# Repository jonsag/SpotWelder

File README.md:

# SpotWelder

A timed circuit controlling an SSR connected to an old microwave transformer.  

Weld time is displayed on an OLED screen, and set with a rotary encoder.

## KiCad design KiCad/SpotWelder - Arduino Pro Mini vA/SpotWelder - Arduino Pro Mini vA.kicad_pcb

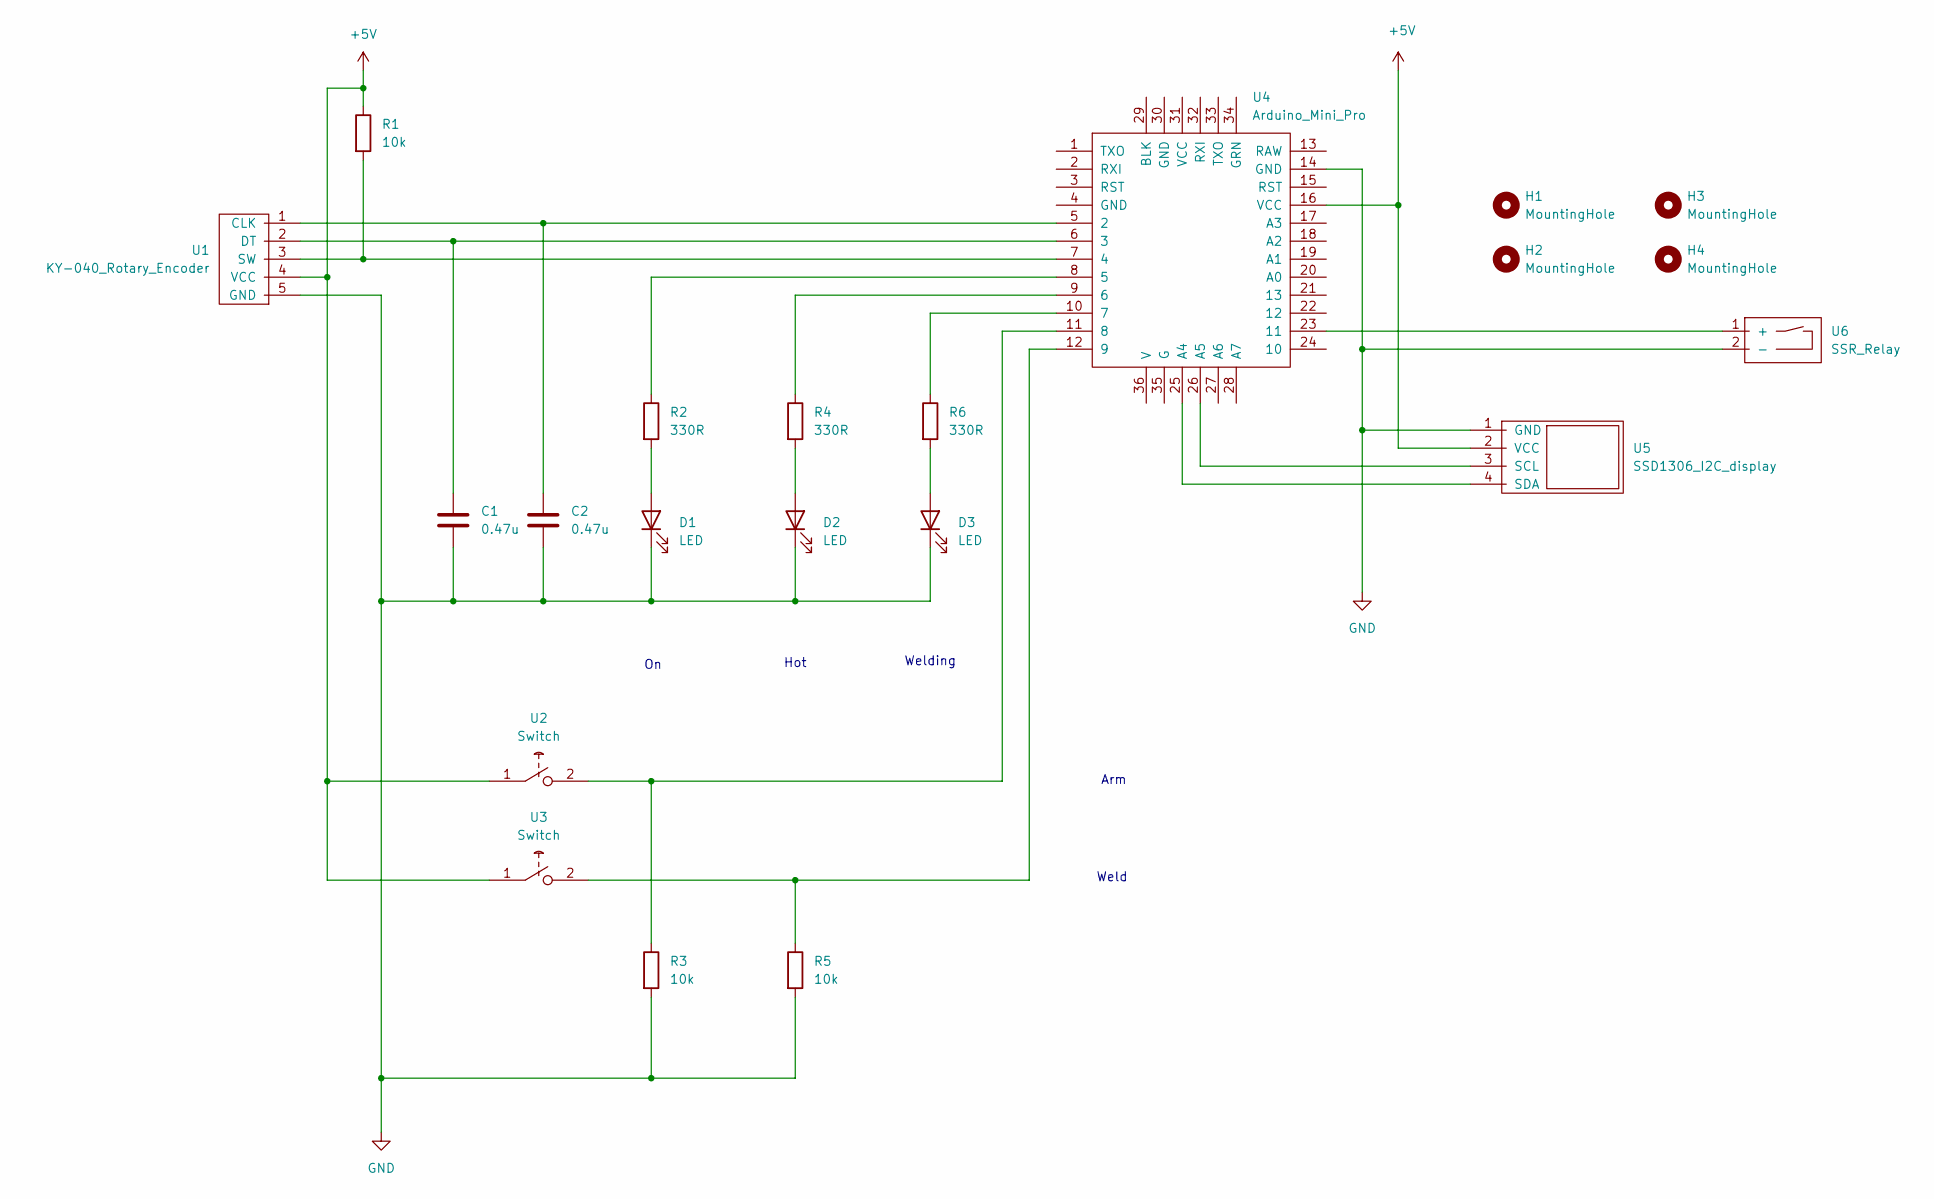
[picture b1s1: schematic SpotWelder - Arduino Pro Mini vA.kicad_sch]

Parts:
C1, C2: 0.47u; C_Disc_D3.8mm_W2.6mm_P2.50mm_large
D1, D2, D3: LED; 2-pin JST LED
H1, H2, H3, H4: MountingHole; MountingHole_3.2mm_M3
R1, R3, R5: 10k; R_Axial_DIN0207_L6.3mm_D2.5mm_P10.16mm_Horizontal_large
R2, R4, R6: 330R; R_Axial_DIN0207_L6.3mm_D2.5mm_P10.16mm_Horizontal_large
U1: KY-040_Rotary_Encoder; 5-pin JST Rotary Encoder
U2, U3: Switch; 2-pin JST Switch
U4: Arduino_Mini_Pro; Arduino_Pro_Mini_vA_sides_n_A4,A5_large
U5: SSD1306_I2C_display; 4-pin JST SSD1306 I2C OLED Display
U6: SSR_Relay; 2-pin JST SSR

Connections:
+5V: R1.1, U1.4 (VCC), U2.1 (Com), U3.1 (Com), U4.16 (VCC), U5.2 (VCC)
GND: C1.2, C2.2, D1.1 (K), D2.1 (K), D3.1 (K), R3.2, R5.2, U1.5 (GND), U4.14 (GND), U5.1 (GND), U6.2 (-)
unnamed: D1.2 (A), R2.2
unnamed: D2.2 (A), R4.2
unnamed: D3.2 (A), R6.2
unnamed: C2.1, U1.1 (CLK), U4.5 (2)
unnamed: C1.1, U1.2 (DT), U4.6 (3)
unnamed: R1.2, U1.3 (SW), U4.7 (4)
unnamed: R3.1, U2.2 (NO), U4.11 (8)
unnamed: R5.1, U3.2 (NO), U4.12 (9)
unnamed: R2.1, U4.8 (5)
unnamed: R4.1, U4.9 (6)
unnamed: R6.1, U4.10 (7)
unnamed: U4.23 (11), U6.1 (+)
unnamed: U4.25 (A4), U5.4 (SDA)
unnamed: U4.26 (A5), U5.3 (SCL)

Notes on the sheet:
Arm
Welding
Hot
Weld

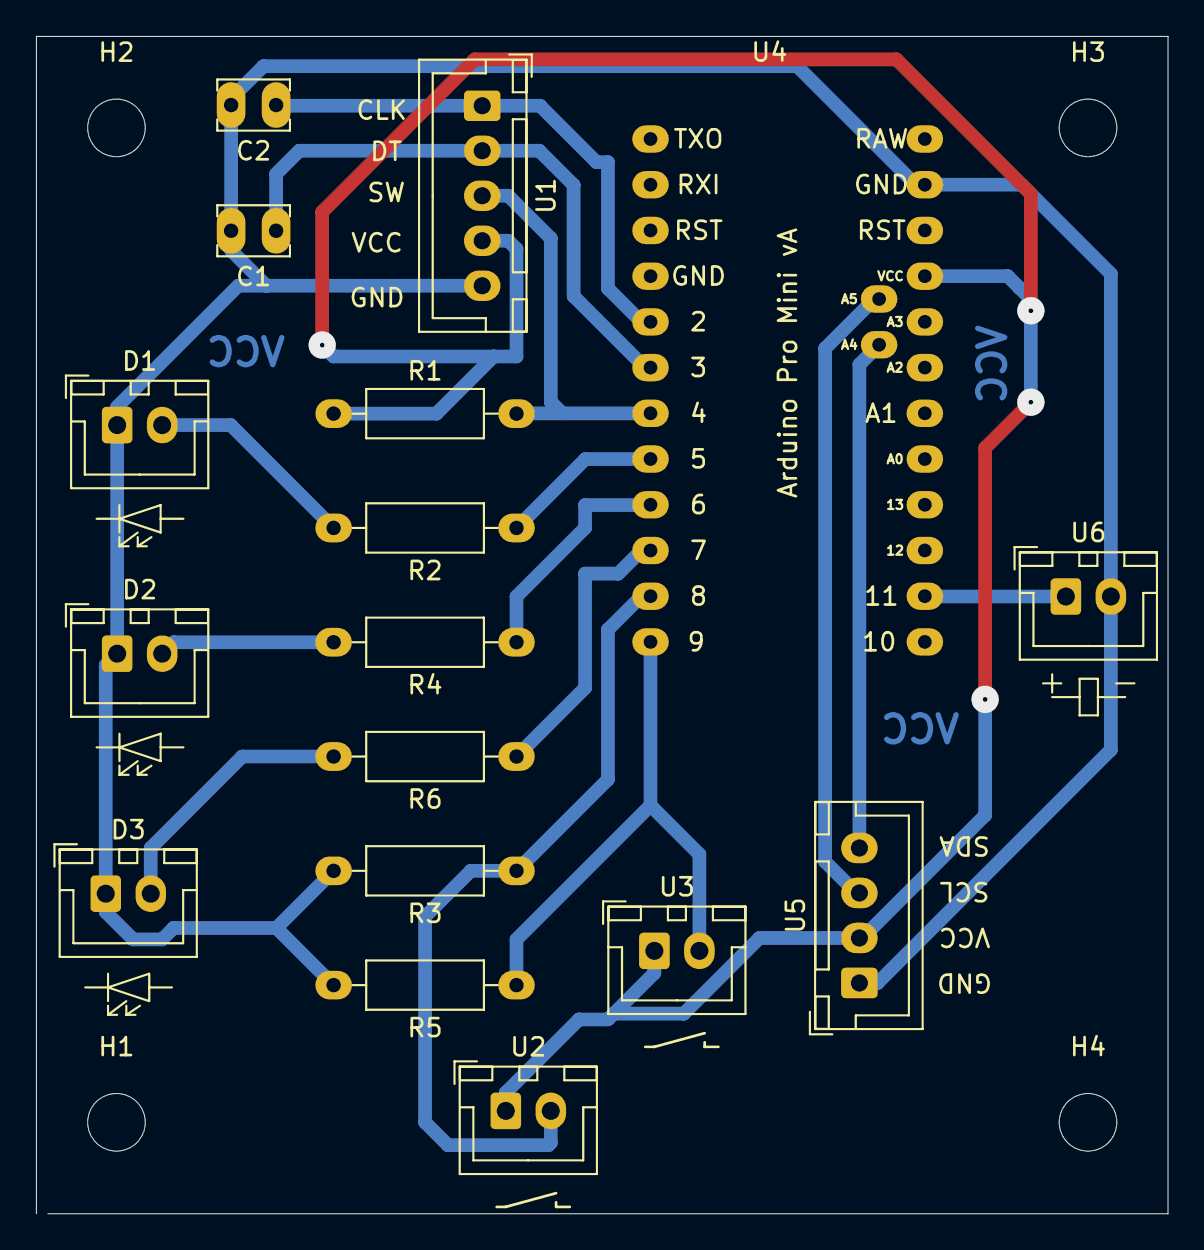
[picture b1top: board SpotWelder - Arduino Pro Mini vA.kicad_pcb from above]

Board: 2 copper layers, 62.9 x 65.4 mm, 21 parts (0 on the bottom side), 16 nets.

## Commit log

2024-12-12 gitignore
2024-12-12 some work
2024-12-13 testing
2024-12-13 renames
2024-12-13 is now welding and writing to screen
2024-12-14 reorganize
2024-12-14 rename
2024-12-15 new sketches
2024-12-15 skipped debounce
2024-12-18 readme
2024-12-19 deletes
